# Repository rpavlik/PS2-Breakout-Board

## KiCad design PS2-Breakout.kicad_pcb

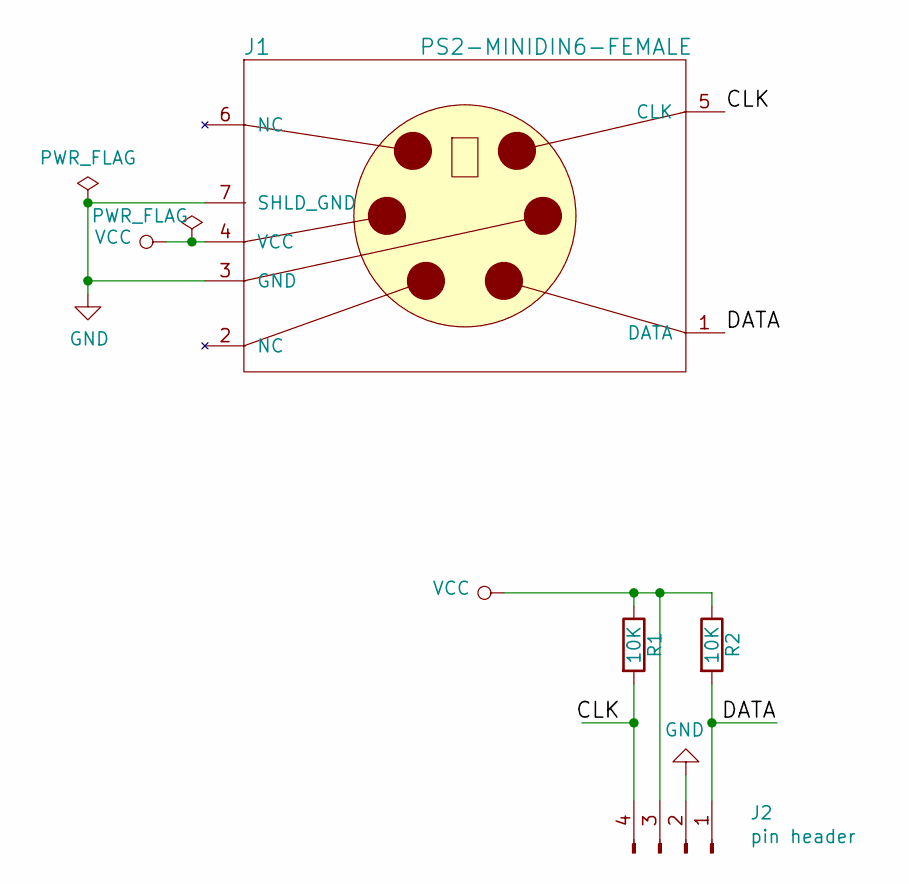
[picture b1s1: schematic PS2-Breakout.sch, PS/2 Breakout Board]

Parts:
J1: PS2-MINIDIN6-FEMALE; MINI-DIN-6-FULL-SHIELD
J2: pin header; PinHeader_1x04_P2.54mm_Vertical
R1, R2: 10K; R_Axial_DIN0207_L6.3mm_D2.5mm_P2.54mm_Vertical

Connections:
/CLK: J1.5 (CLK), J2.4, R1.2
/DATA: J1.1 (DATA), J2.1, R2.2
GND: J1.3 (GND), J1.7 (SHLD_GND), J2.2
VCC: J1.4 (VCC), J2.3, R1.1, R2.1

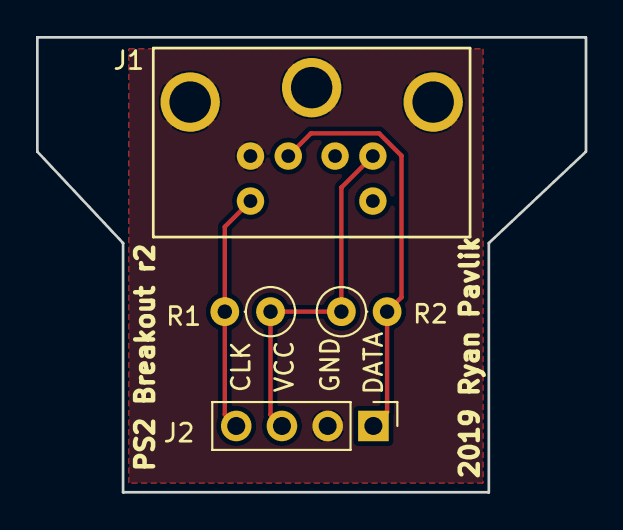
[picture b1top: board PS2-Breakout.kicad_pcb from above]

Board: 2 copper layers, 30.5 x 25.3 mm, 4 parts (0 on the bottom side), 4 nets.

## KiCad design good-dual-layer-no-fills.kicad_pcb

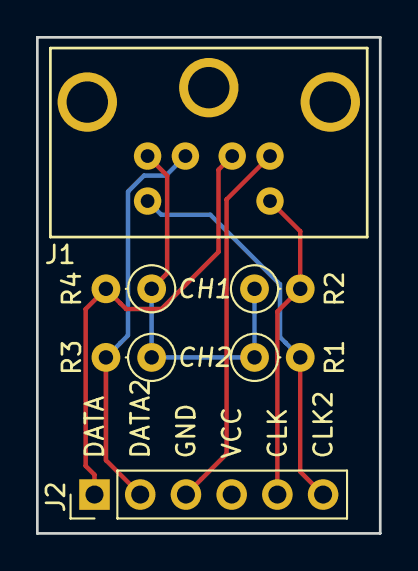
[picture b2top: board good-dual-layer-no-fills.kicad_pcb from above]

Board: 2 copper layers, 19.1 x 27.6 mm, 6 parts (0 on the bottom side), 6 nets.

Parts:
J1: PS2-MINIDIN6-FEMALE; MINI-DIN-6-FULL-SHIELD
J2: PIN_CONNECTOR; Pin_Header_Straight_1x06_Pitch2.54mm
R1, R2, R3, R4: 10K; R_Axial_DIN0207_L6.3mm_D2.5mm_P2.54mm_Vertical

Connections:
/CLK: J1.5, J2.5, R2.2
/CLK2: J1.6, J2.6, R1.2
/DATA: J1.1, J2.1, R4.2
/DATA2: J1.2, J2.2, R3.2
/VCC: J1.4, J2.4, R1.1, R2.1, R3.1, R4.1
GND: J1.3, J1.7, J2.3

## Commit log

2017-07-26 Initial commit - gitignore backups and gerber/drill
2017-07-26 Revision 1 plus some alternate historical layouts.
2017-07-26 Remove old backup copies of pcb
2017-07-26 Add and use the custom component/footprint in this project.
2017-07-26 Add script for git clean/smudge filters
2017-07-26 Update gitignore
2017-07-26 commit gitattributes
2017-07-26 Commit changes performed by gitattributes clean filter.
2019-10-01 Fix footprint
2019-10-01 Update to new kicad, and fix layout
2019-10-01 Remove rescue lib
2019-10-01 start of advanced schematic
2019-10-01 Simplify to just channel 1
